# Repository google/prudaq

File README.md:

## Documentation is on the [Wiki](https://github.com/google/prudaq/wiki)

*This is not an official Google product.*

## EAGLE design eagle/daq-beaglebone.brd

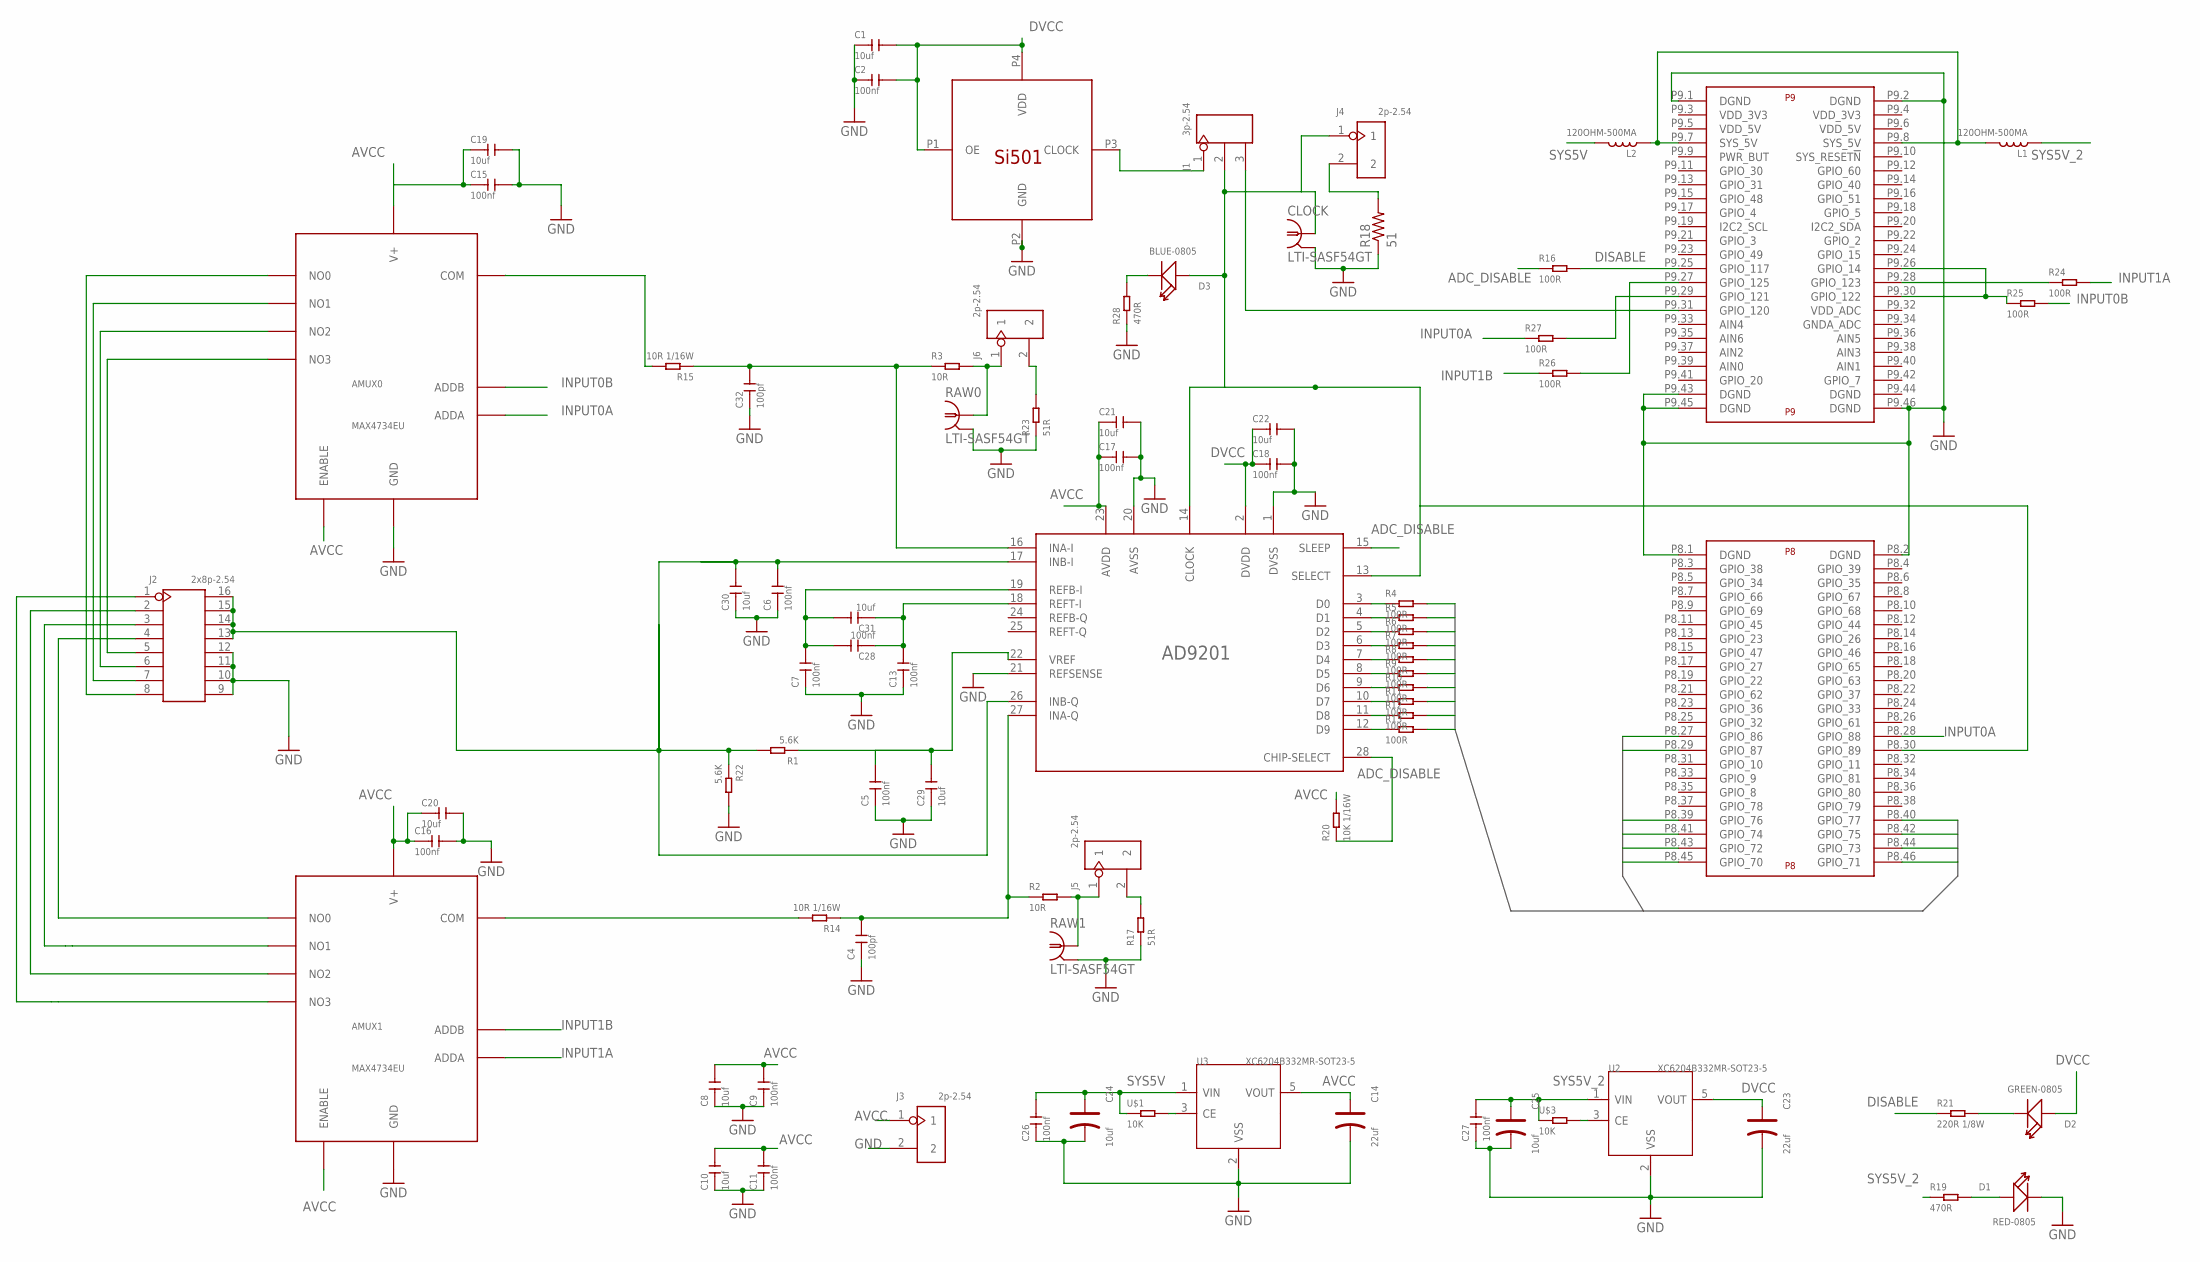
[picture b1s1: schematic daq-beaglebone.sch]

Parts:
AD9201: AD9201; SSOP28
AMUX0, AMUX1: MAX4734EU; UMAX10
C1, C8, C10, C19, C20, C21, C22, C29, C30, C31: 10uf; C0402
C2, C5, C6, C7, C9, C11, C13, C15, C16, C17, C18, C26, C27, C28: 100nf; C0402
C4, C32: 100pf; C0402
C14, C23: 22uf; AVX-A
C24, C25: 10uf; AVX-A
CLOCK: LTI-SASF54GT
D1: RED-0805; LED-0805
D2: GREEN-0805; LED-0805
D3: BLUE-0805; LED-0805
J1: 3p-2.54; H3-2.54
J2: 2x8p-2.54; H2X8-2.54
J3, J4, J5, J6: 2p-2.54; H2-2.54
L1, L2: 120OHM-500MA; L0603
R1, R22: 5.6K; R0402
R2, R3: 10R; R0402
R4, R5, R6, R7, R8, R9, R10, R11, R12, R13, R16, R24, R25, R26, R27: 100R; R0402
R14, R15: 10R 1/16W; R0402
R17, R23: 51R; R0603
R18: 51; R1206
R19, R28: 470R; R0402
R20: 10K 1/16W; R0402
R21: 220R 1/8W; R0402
RAW0, RAW1: LTI-SASF54GT
U2, U3: XC6204B332MR-SOT23-5; SOT-23-5
U$1, U$3: 10K; R0402
U$2: BEAGLE_BONE_BLACK_CAPE
U$4: SI501; 2X2.5DFN

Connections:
ADC_DISABLE: AD9201.15 (SLEEP), AD9201.28 (CHIP-SELECT), R16.1, R20.1
AVCC: AD9201.23 (AVDD), AMUX0.P$5 (ENABLE), AMUX0.P$6 (V+), AMUX1.P$5 (ENABLE), AMUX1.P$6 (V+), C8.2, C9.2, C10.2, C11.2, C14.+, C15.1, C16.1, C17.1, C19.1, C20.1, C21.1, J3.1, R20.2, U3.5 (VOUT)
CLOCK: AD9201.13 (SELECT), AD9201.14 (CLOCK), CLOCK.1, D3.+, J1.2, J4.1, U$2.P8.30 (GPIO_89)
D0: R4.2, U$2.P8.45 (GPIO_70)
D1: R5.2, U$2.P8.46 (GPIO_71)
D2: R6.2, U$2.P8.43 (GPIO_72)
D3: R7.2, U$2.P8.44 (GPIO_73)
D4: R8.2, U$2.P8.41 (GPIO_74)
D5: R9.2, U$2.P8.42 (GPIO_75)
D6: R10.2, U$2.P8.39 (GPIO_76)
D7: R11.2, U$2.P8.40 (GPIO_77)
D8: R12.2, U$2.P8.27 (GPIO_86)
D9: R13.2, U$2.P8.29 (GPIO_87)
DISABLE: R16.2, R21.1, U$2.P9.25 (GPIO_117)
DVCC: AD9201.2 (DVDD), C1.2, C2.2, C18.1, C22.1, C23.+, D2.+, U2.5 (VOUT), U$4.P1 (OE), U$4.P4 (VDD)
GND: AD9201.1 (DVSS), AD9201.20 (AVSS), AD9201.21 (REFSENSE), AMUX0.P$3 (GND), AMUX1.P$3 (GND), C1.1, C2.1, C4.1, C5.1, C6.1, C7.1, C8.1, C9.1, C10.1, C11.1, C13.1, C14.-, C15.2, C16.2, C17.2, C18.2, C19.2, C20.2, C21.2, C22.2, C23.-, C24.-, C25.-, C26.1, C27.1, C29.1, C30.1, C32.1, CLOCK.2, CLOCK.3 (2), CLOCK.4 (2), CLOCK.5 (2), D1.-, J2.9, J2.10, J2.11, J2.12, J3.2, R17.1, R18.1, R22.2, R23.1, R28.1, RAW0.2, RAW0.3 (2), RAW0.4 (2), RAW0.5 (2), RAW1.2, RAW1.3 (2), RAW1.4 (2), RAW1.5 (2), U2.2 (VSS), U3.2 (VSS), U$2.P8.1 (DGND), U$2.P8.2 (DGND), U$2.P9.1 (DGND), U$2.P9.2 (DGND), U$2.P9.43 (DGND), U$2.P9.45 (DGND), U$2.P9.46 (DGND), U$4.P2 (GND)
INPUT0A: AMUX0.P$1 (ADDA), R27.1, U$2.P8.28 (GPIO_88)
INPUT0B: AMUX0.P$10 (ADDB), R25.2
INPUT1A: AMUX1.P$1 (ADDA), R24.2
INPUT1B: AMUX1.P$10 (ADDB), R26.1
unnamed: AD9201.3 (D0), R4.1
unnamed: AD9201.4 (D1), R5.1
unnamed: AMUX0.P$2 (NO0), J2.8
unnamed: AD9201.17 (INB-I), AD9201.26 (INB-Q), C6.2, C30.2, J2.13, J2.14, J2.15, J2.16, R1.2, R22.1
unnamed: AD9201.22 (VREF), C5.2, C29.2, R1.1
unnamed: AD9201.18 (REFT-I), C13.2, C28.1, C31.1
unnamed: AD9201.19 (REFB-I), C7.2, C28.2, C31.2
unnamed: AMUX0.P$9 (NO1), J2.7
unnamed: R25.1, U$2.P9.26 (GPIO_14), U$2.P9.30 (GPIO_122)
unnamed: AMUX1.P$8 (COM), R14.2
unnamed: AD9201.16 (INA-I), C32.2, R3.1, R15.1
unnamed: AD9201.5 (D2), R6.1
unnamed: AD9201.6 (D3), R7.1
unnamed: AD9201.7 (D4), R8.1
unnamed: AD9201.8 (D5), R9.1
unnamed: AD9201.9 (D6), R10.1
unnamed: AD9201.10 (D7), R11.1
unnamed: AD9201.11 (D8), R12.1
unnamed: AD9201.12 (D9), R13.1
unnamed: J1.1, U$4.P3 (CLOCK)
unnamed: J1.3, U$2.P9.31 (GPIO_120)
unnamed: AMUX0.P$8 (COM), R15.2
unnamed: AD9201.27 (INA-Q), C4.2, R2.1, R14.1
unnamed: R27.2, U$2.P9.29 (GPIO_121)
unnamed: AMUX0.P$4 (NO2), J2.6
unnamed: AMUX0.P$7 (NO3), J2.5
unnamed: D1.+, R19.2
unnamed: J5.1, R2.2, RAW1.1
unnamed: AMUX1.P$4 (NO2), J2.2
unnamed: D3.-, R28.2
unnamed: D2.-, R21.2
unnamed: J6.1, R3.2, RAW0.1
unnamed: J4.2, R18.2
unnamed: U2.3 (CE), U$3.2
unnamed: U3.3 (CE), U$1.2
unnamed: R24.1, U$2.P9.28 (GPIO_123)
unnamed: R26.2, U$2.P9.27 (GPIO_125)
unnamed: J5.2, R17.2
unnamed: J6.2, R23.2
unnamed: AMUX1.P$2 (NO0), J2.4
unnamed: AMUX1.P$9 (NO1), J2.3
unnamed: AMUX1.P$7 (NO3), J2.1
OTHERSYS5V: L1.2, L2.1, U$2.P9.7 (SYS_5V), U$2.P9.8 (SYS_5V)
SYS5V: C24.+, C26.2, L2.2, U3.1 (VIN), U$1.1
SYS5V_2: C25.+, C27.2, L1.1, R19.1, U2.1 (VIN), U$3.1

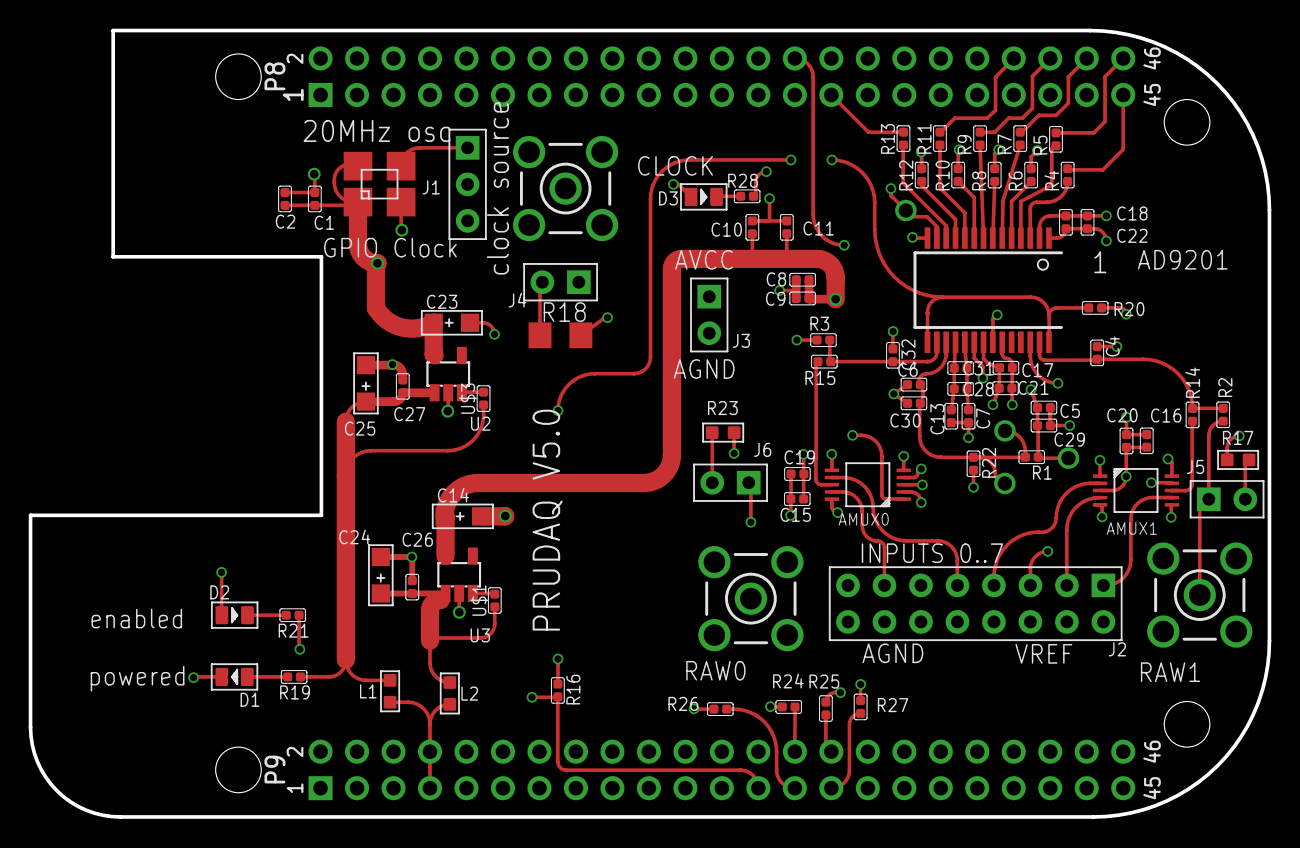
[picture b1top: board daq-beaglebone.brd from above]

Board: 4 copper layers, 86.2 x 54.8 mm, 81 parts (0 on the bottom side), 65 nets.

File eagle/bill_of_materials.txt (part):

Partlist exported from daq-beaglebone.sch at 1/4/16 11:44 AM

Qty Value                  Device                                  Package                Parts                                                           Description                          MF MPN                    OC_FARNELL OC_NEWARK VALUE               
11  100R                   SMD-RES-100R-5%-1/16W(0402)             R0402                  R4, R5, R6, R7, R8, R9, R10, R11, R12, R13, R16                 301010028                               RC0402JR-07100RL                            100R                
4   100R                   SMD-RES-33R-1%-1/16W(0402)              R0402                  R24, R25, R26, R27                                              301010609                               RC0402FR-0733RL                             33R                 
14  100nf                  CERAMIC-100NF-25V-10%-X7R(0402)         C0402                  C2, C5, C6, C7, C9, C11, C13, C15, C16, C17, C18, C26, C27, C28 302010024                               CC0402KRX7R8BB104                           100nf               
2   100pf                  CERAMIC-100PF-50V-5%-NPO(0402)          C0402                  C4, C32                                                         302010012                               CC0402JRNPO9BN101                           100pf               
2   10K                    SMD-RES-10K-5%-1/(0402)                 R0402                  U$1, U$3                                                        301010004                               RC0402JR-0710KL                             10K                 
1   10K 1/16W              SMD-RES-10K-1%-1/16W(0402)              R0402                  R20                                                             301010047                               RC0402FR-0710KL                             10K 1/16W           
2   10R                    SMD-RES-0R-5%-1/16W(0402)               R0402                  R2, R3                                                          301010000                               RC0402JR-070RL                              0R                  
2   10R 1/16W              SMD-RES-10R-1%-1/16W(0402)              R0402                  R14, R15                                                        301010444                               RC0402FR-0710RL                             10R 1/16W           
10  10uf                   CERAMIC-10UF-6.3V-20%-X5R(0402)         C0402                  C1, C8, C10, C19, C20, C21, C22, C29, C30, C31                  302010053                               CC0402MRX5R5BB106                           10uf                
2   10uf                   TANTALUM-SMD-10UF-10V-10%(AVX-A)        AVX-A                  C24, C25                                                        302020011                               TAJA106K010RNJ                              10uf                
2   120OHM-500MA           SMD-FERRITE-CHIP-120-OHM-500MA(0603)    L0603                  L1, L2                                                          303030001                               BLM18AG121SN1D                              120OHM-500MA        
1   220R 1/8W              SMD-RES-220R-1%-1/8W(0402)              R0402                  R21                                                             301010550                               RC0402FR-07220RL                            220R 1/8W           
2   22uf                   TANTALUM-SMD-22UF-6.3V(AVX-A)           AVX-A                  C14, C23                                                        302020009                               TAJA226K006RNJ                              22uf                
1   2p-2.54                DIP-BLACK-FEMALE-HEADER-VERT(2P-2.54)   H2-2.54                J3                                                              320030023                               F185-1102A1BSYA1                            2p-2.54             
3   2p-2.54                DIP-BLACK-MALE-HEADER-VERT(2P-2.54)     H2-2.54                J4, J5, J6                                                      320020016                               P125-1102A0BS116A1                          2p-2.54             
1   2x8p-2.54              DIP-BLACK-FEMALE-HEADER-VERT(2X8P-2.54) H2X8-2.54              J2                                                              320030080                               F185-1216A0BSYA1                            2x8p-2.54           
1   3p-2.54                DIP-BLACK-FEMALE-HEADER-VERT(3P-2.54)   H3-2.54                J1                                                              320030024                               F185-1103A0BSYA1                            3p-2.54             
2   470R                   SMD-RES-470R-1%-1/16W(0402)             R0402                  R19, R28                                                        301010012                               RC0402FR-07470RL                            470R                
2   5.6K                   SMD-RES-5.6K-1%-1/10W(0402)             R0402                  R1, R22                                                         301010546                               CRCW04025K60FKED                            5.6K                
1   51                     R-US_R1206                              R1206                  R18                                                             RESISTOR, American symbol                                                                               
2   51R                    SMD-RES-51R-1%-1/10W(0603)              R0603                  R17, R23                                                        301010225                               RC0603FR-0751RL                             51R                 
1   AD9201                 AD9201                                  SSOP28                 AD9201                                                          AD9201                                                                                                  
1   BEAGLE_BONE_BLACK_CAPE BEAGLE_BONE_BLACK_CAPE                  BEAGLE_BONE_BLACK_CAPE U$2                                                                                                                                                                     
1   BLUE-0805              SMD-LED-CLEAR-RED(0805)                 LED-0805               D3                                                              304090046                               17-215SURC/S530-A2/TR8                      RED-0805            
1   GREEN-0805             SMD-LED-CLEAR-GREEN(0805)               LED-0805               D2                                                              304090057                               17-215SYGC/S530-E2/TR8                      GREEN-0805          
3   LTI-SASF54GT           LTI-SASF54GT                            LTI-SASF54GT           CLOCK, RAW0, RAW1                                               SMA vertical PCB thrue hole jack                               unknown    unknown                       
2   MAX4734EU              MAX4734EU                               UMAX10                 AMUX0, AMUX1                                                    4:1 analog switch in uMax 10 package                                                                    
1   RED-0805               SMD-LED-CLEAR-RED(0805)                 LED-0805               D1                                                              304090046                               17-215SURC/S530-A2/TR8                      RED-0805            
1   SI501                  SI501                                   2X2.5DFN               U$4                                                             501JCA20M0000DAFR                                                                                       
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
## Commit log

2016-01-04 Init copy schematics/layout, analog capture code, bom, readme, license
2016-01-28 Two board modifications
    Describe how to modify the board to support single channel readout and differential input.
2016-01-28 Theory of operation for the board
    Clock, input selection, power supply overview
2016-01-28 figures for board docs
2016-01-28 Analog input diagram
2016-01-28 Describes two board mods
    Differential input support and control of channel readout
2016-01-28 Theory of operation for the board
2016-01-29 Removing doc/ from image paths
2016-01-29 Fixing differential input mod image
2016-01-29 Create InputOutput.md
    Describes GPIO pin assignments and how the PRUs talk to the ADC.
2016-02-25 Simplified schematic shows how the 8 inputs work
2016-02-25 Wrong name
2016-02-25 Flesh out input channel selection
2016-03-02 minor formatting
2016-03-02 Code cleanup, commenting, and error checking
2016-03-03 Clean up comments and README.md
2016-03-04 Remove extraneous backslash
2016-03-05 clean up disused pru code, rename to pru0.p and pru1.p, make pru1.p read both channels efficiently
2016-03-05 minor: list pru0.bin before pru1.bin lest anyone think it's significant
2016-03-11 Tips on how to separate select from clock
2016-03-11 20MHz -> 10MHz (20MHz clock was uncomfortably tight)
2016-03-11 performance.png
2016-03-11 Performance issues
2016-03-11 Text of the performance doc
2016-03-11 capitalization
2016-03-15 minor; mention sudo
2016-03-16 add round robin example
2016-03-18 fix formatting
2016-03-18 Rewrite main README.
    Includes a link to QuickStart that doesn't exist yet but which should cover the stuff that used to be here.
2016-03-18 Remove extraneous commands
2016-03-19 Fix minor nits
2016-03-19 Reorder sections
2016-03-19 Connecting inputs 0 and 4 to agnd and vref
2016-03-19 Improvements to setup.sh and prudaq_capture.c
2016-03-26 Paste in sample output
2016-03-26 Mention email list
2016-05-13 Add PNGs of schematic and layout for casual access
2016-05-14 Schematic and layout PNGs for those without eagle
    File... Export... Image. Then 300dpi for the schematic and 600dpi for the layout.
2016-05-26 Moving docs to the wiki
2016-06-11 add hardware self test
2016-06-11 minor fixes to selftest
2016-06-13 Make errors more helpful
2016-07-12 Added setup script for use with BeagleLogic system image
2016-07-12 Making sure beaglelogic is set for continuous capture
2016-07-12 Bolder pointer to the wiki
2016-08-31 Fix data corruption when buf rolls over. h/t mattvenn.

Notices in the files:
parts and their libraries:
SparkFun-Boards: Licensing: Creative Commons ShareAlike 4.0 International - https://creativecommons.org/licenses/by-sa/4.0
